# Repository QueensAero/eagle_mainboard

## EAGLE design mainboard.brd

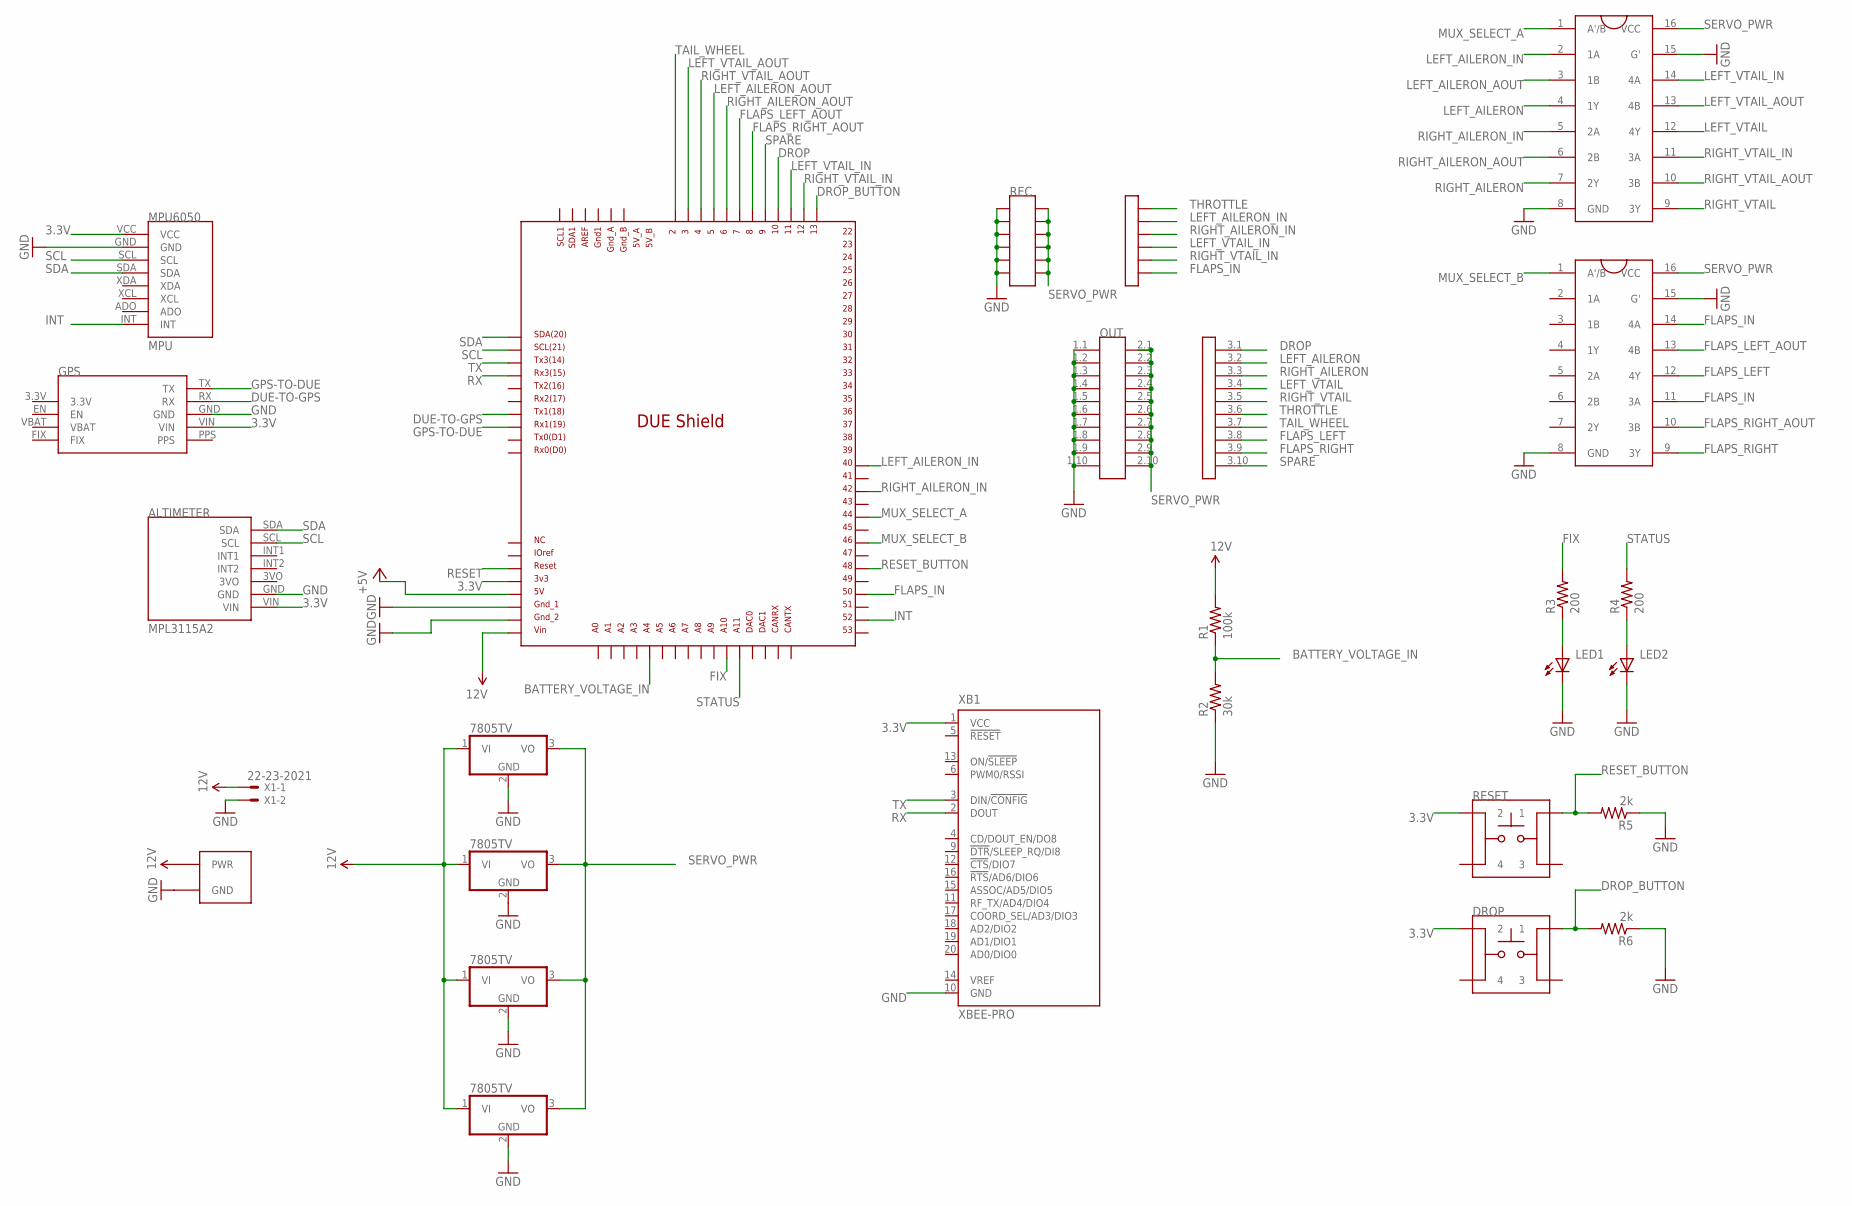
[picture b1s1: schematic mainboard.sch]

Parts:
DROP: PUSHBUTTON
G1: GPS_ADAFRUIT
IC1, IC2, IC3, IC4: 7805TV; TO220V
LED1, LED2: LED5MM
MPU: MPU6050
MUX1, MUX2: SN74HC157
OUT: PIN_3X10
R1: 100k; 0204/7
R2: 30k; 0204/7
R3, R4: 200; 0204/7
R5, R6: 2k; 0204/7
REC: PIN_3X6
RESET: PUSHBUTTON
U$1: DUE(NORMAL)
U$3: PWR-BATT
U$4: ALTIMETER_V5
X1: 22-23-2021
XB1: XBEE-PRO

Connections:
3.3V: DROP.2, G1.VIN, MPU.VCC, RESET.2, U$1.3V3, U$4.VIN, XB1.1 (VCC)
12V: IC1.1 (VI), IC2.1 (VI), IC3.1 (VI), IC4.1 (VI), R1.2, U$1.VIN, U$3.PWR, X1.1
+5V: U$1.5V
BATTERY_VOLTAGE_IN: R1.1, R2.2, U$1.A4
DROP: OUT.3.1, U$1.10
DROP_BUTTON: DROP.1, R6.2, U$1.13
DUE-TO-GPS: G1.RX, U$1.TX1
FIX: R3.2, U$1.A10
FLAPS_IN: MUX2.11 (3A), MUX2.14 (4A), REC.3.6, U$1.50
FLAPS_LEFT: MUX2.12 (4Y), OUT.3.8
FLAPS_LEFT_AOUT: MUX2.13 (4B), U$1.7
FLAPS_RIGHT: MUX2.9 (3Y), OUT.3.9
FLAPS_RIGHT_AOUT: MUX2.10 (3B), U$1.8
GND: G1.GND, IC1.2 (GND), IC2.2 (GND), IC3.2 (GND), IC4.2 (GND), LED1.K (C), LED2.K (C), MPU.GND, MUX1.8 (GND), MUX1.15 (G'), MUX2.8 (GND), MUX2.15 (G'), OUT.1.1, OUT.1.2, OUT.1.3, OUT.1.4, OUT.1.5, OUT.1.6, OUT.1.7, OUT.1.8, OUT.1.9, OUT.1.10, R2.1, R5.1, R6.1, REC.1.1, REC.1.2, REC.1.3, REC.1.4, REC.1.5, REC.1.6, U$1.GND_1, U$1.GND_2, U$3.GND, U$4.GND, X1.2, XB1.10 (GND)
GPS-TO-DUE: G1.TX, U$1.RX1
INT: MPU.INT, U$1.52
LEFT_AILERON: MUX1.4 (1Y), OUT.3.2
LEFT_AILERON_AOUT: MUX1.3 (1B), U$1.5
LEFT_AILERON_IN: MUX1.2 (1A), REC.3.2, U$1.40
LEFT_VTAIL: MUX1.12 (4Y), OUT.3.4
LEFT_VTAIL_AOUT: MUX1.13 (4B), U$1.3
LEFT_VTAIL_IN: MUX1.14 (4A), REC.3.4, U$1.11
MUX_SELECT_A: MUX1.1 (A'/B), U$1.44
MUX_SELECT_B: MUX2.1 (A'/B), U$1.46
unnamed: LED1.A, R3.1
unnamed: LED2.A, R4.1
RESET: U$1.RESET
RESET_BUTTON: R5.2, RESET.1, U$1.48
RIGHT_AILERON: MUX1.7 (2Y), OUT.3.3
RIGHT_AILERON_AOUT: MUX1.6 (2B), U$1.6
RIGHT_AILERON_IN: MUX1.5 (2A), REC.3.3, U$1.42
RIGHT_VTAIL: MUX1.9 (3Y), OUT.3.5
RIGHT_VTAIL_AOUT: MUX1.10 (3B), U$1.4
RIGHT_VTAIL_IN: MUX1.11 (3A), REC.3.5, U$1.12
RX: U$1.RX3, XB1.2 (DOUT)
SCL: MPU.SCL, U$1.SCL, U$4.SCL
SDA: MPU.SDA, U$1.SDA, U$4.SDA
SERVO_PWR: IC1.3 (VO), IC2.3 (VO), IC3.3 (VO), IC4.3 (VO), MUX1.16 (VCC), MUX2.16 (VCC), OUT.2.1, OUT.2.2, OUT.2.3, OUT.2.4, OUT.2.5, OUT.2.6, OUT.2.7, OUT.2.8, OUT.2.9, OUT.2.10, REC.2.1, REC.2.2, REC.2.3, REC.2.4, REC.2.5, REC.2.6
SPARE: OUT.3.10, U$1.9
STATUS: R4.2, U$1.A11
TAIL_WHEEL: OUT.3.7, U$1.2
THROTTLE: OUT.3.6, REC.3.1
TX: U$1.TX3, XB1.3 (DIN/!CONFIG)

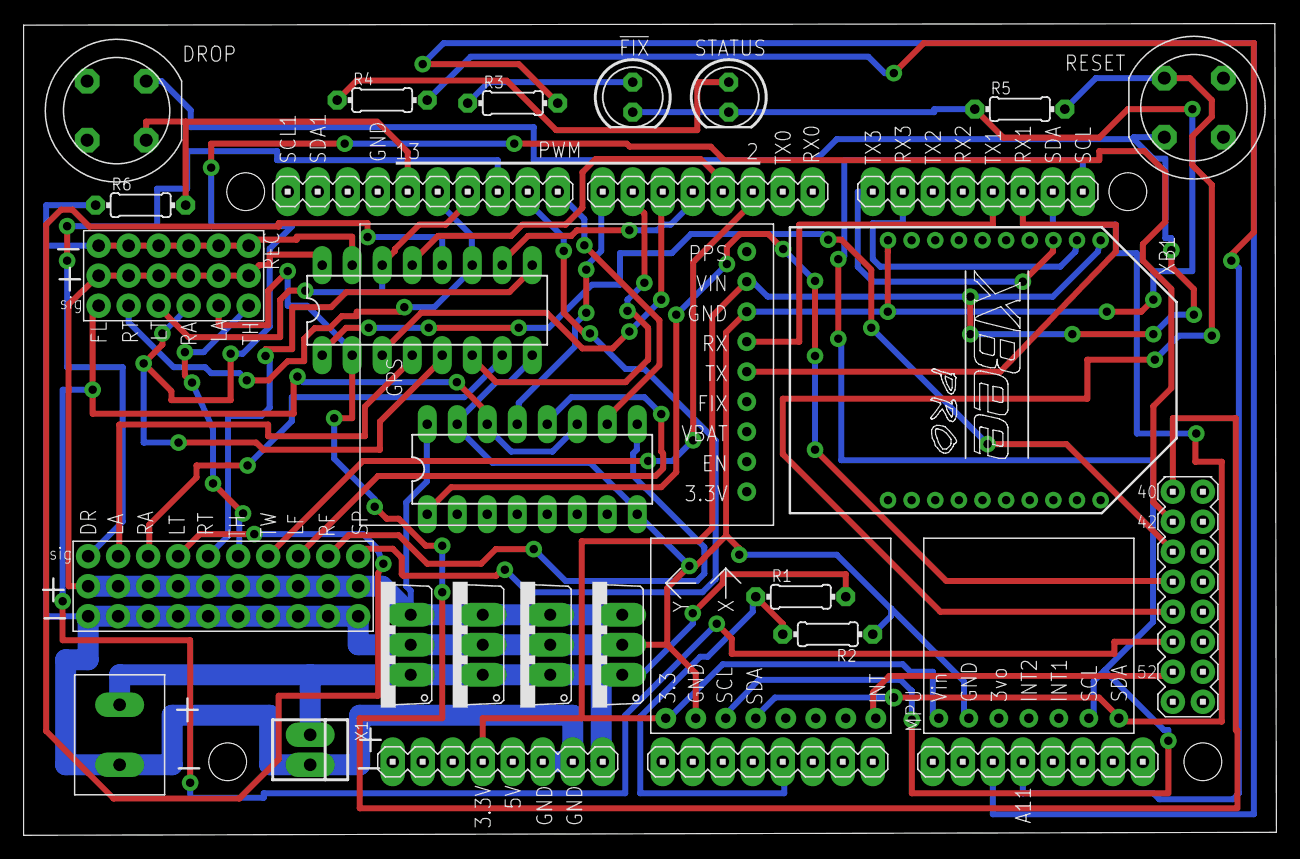
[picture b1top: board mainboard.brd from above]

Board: 2 copper layers, 106.0 x 68.7 mm, 25 parts (0 on the bottom side), 41 nets.

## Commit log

2015-11-26 2014-2015 mainboard eagle files
2015-12-01 Updated sensors
2016-01-06 add gps footprint to board
2016-01-27 Fix servo connections and remove unnecessary parts
    changes from Schindeler's feedback
2016-01-29 Update labels on board and servo connections
2016-02-10 final updates
2016-11-24 Remove Old Version
    Want clean upload of only mainboard and schematic files
2016-11-24 Remove Old Versions
    Want clean upload of only mainboard and schematic files
2016-11-24 Remove Old Files
    Want clean upload of only mainboard and schematic files
2016-11-24 Added 2016-2017 version of the board
2016-11-30 Board with Four Holes
    Added top-right and bottom-left hole
    Hole placement based on Arduino due eagle file found on Arduino.com
2016-12-02 ERC error fixed
2016-12-09 Board 2016-2017

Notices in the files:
parts and their libraries:
SparkFun-Aesthetics: Licensing: Creative Commons ShareAlike 4.0 International - https://creativecommons.org/licenses/by-sa/4.0
